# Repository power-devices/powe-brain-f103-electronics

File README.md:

# Welcome to the Power BrainF103 electronics repository

I teach power electronics and I want to provide my students the best experience possible. This is the reason I created this project. I intend to allow people to produce power electronics devices at an extreme low cost. This board required 4 layers, but this is no problem today due to [JLCPCB](https://jlcpcb.com/) or other manufacturers.

So far, the project is divided into 3 pieces:

 1. Power supply: used to delivery power the other boards, it is compatible with mono-three phase up to 220 VAC
 2. Power bullet: a three phase h-bridge, simple as that
 3. Power brain F103: the main controller

# Disclaimer

I provide no warranty at all. Use it at your own risk!

# What will I find here?

You will find the design and production files. To edit the schematic/board you will need to install Kicad. I used version 7 to create this board.

# What can I do with this?

In this repository the board design and production files are stored. You are welcome to download/distribute it, use it, whatever.

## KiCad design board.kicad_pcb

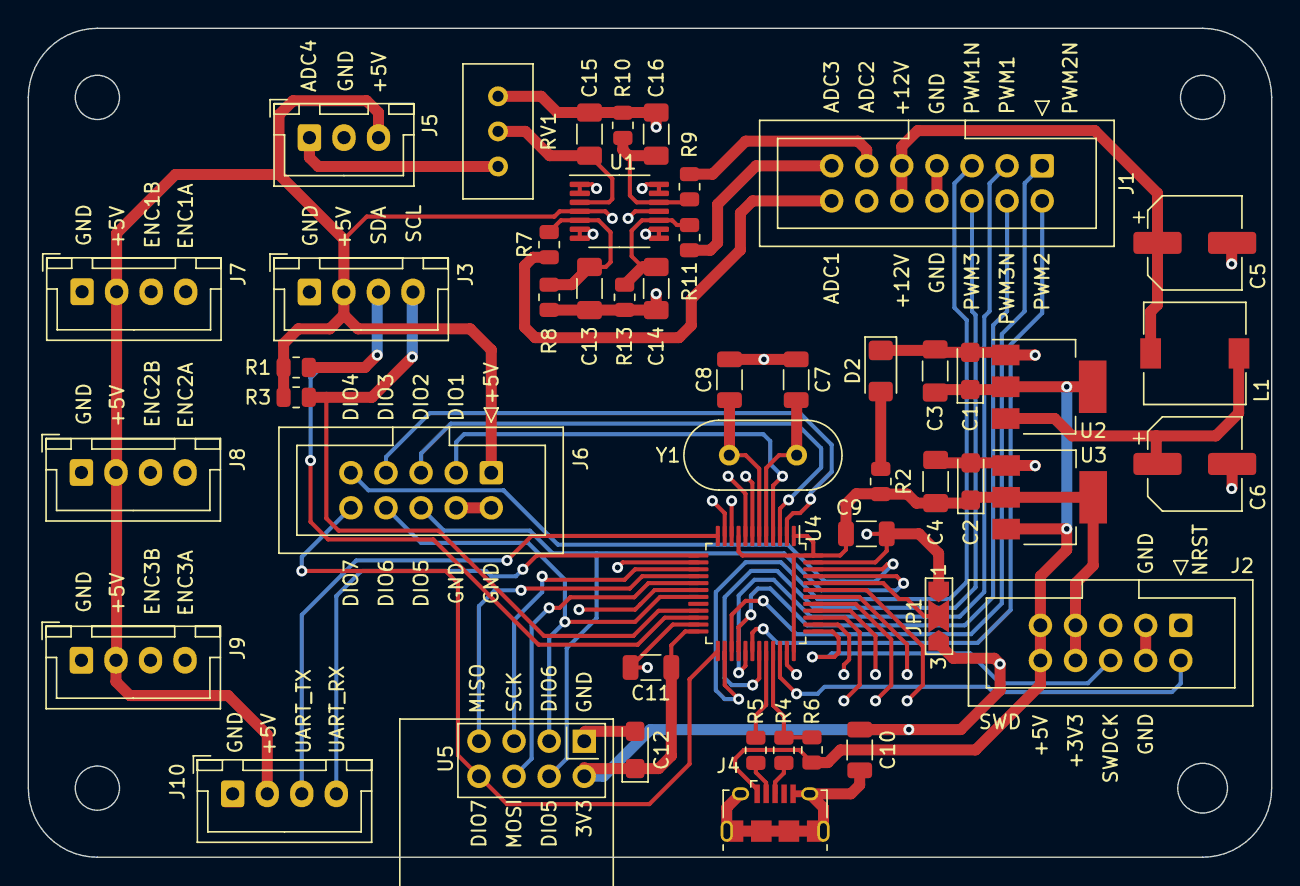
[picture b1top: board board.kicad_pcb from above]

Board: 4 copper layers, 90.0 x 60.0 mm, 48 parts (0 on the bottom side), 54 nets.

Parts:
C1, C2, C12: 10uF; CP_EIA-3216-18_Kemet-A
C3, C4: 1uF; C_1206_3216Metric_Pad1.33x1.80mm_HandSolder
C5, C6: 100uF; CP_Elec_6.3x7.7
C7, C8: 22pF; C_1206_3216Metric
C9: 1uF; C_1206_3216Metric
C10, C11: 100nF; C_1206_3216Metric
C13, C14, C15, C16: 10nF; C_1206_3216Metric_Pad1.33x1.80mm_HandSolder
D2: LED; LED_1206_3216Metric_Pad1.42x1.75mm_HandSolder
J1: Conn_02x07_Odd_Even; IDC-Header_2x07_P2.54mm_Vertical
J2: SWD; IDC-Header_2x05_P2.54mm_Vertical
J3: I2C; JST_XH_B4B-XH-A_1x04_P2.50mm_Vertical
J4: USB_B_Micro; USB_Micro-B_Amphenol_10118194_Horizontal
J5: ADC_CH4; JST_XH_B3B-XH-A_1x03_P2.50mm_Vertical
J6: GPIO; IDC-Header_2x05_P2.54mm_Vertical
J7, J8, J9: ENCODER; JST_XH_B4B-XH-A_1x04_P2.50mm_Vertical
J10: UART; JST_XH_B4B-XH-A_1x04_P2.50mm_Vertical
JP1: SolderJumper-3_P2.0mm_Open_TrianglePad1.0x1.5mm_NumberLabels
L1: 100uH; L_7.3x7.3_H4.5
R1, R3: 3k3; R_0805_2012Metric
R2: 470R; R_0805_2012Metric
R4, R5: 22R; R_0805_2012Metric
R6: 1k5; R_0805_2012Metric
R7, R9, R11: 47k; R_0805_2012Metric
R8, R10, R13: 91k; R_0805_2012Metric
RV1: 10k; Potentiometer_Bourns_3296W_Vertical
U1: LM324; TSSOP-14_4.4x5mm_P0.65mm
U2: AMS1117-5.0; SOT-223-3_TabPin2
U3: AMS1117-3.3; SOT-223-3_TabPin2
U4: STM32F103C8Tx; LQFP-48_7x7mm_P0.5mm
U5: NRF24L01; nRF24L01_Breakout
Y1: 16MHz; Crystal_HC49-4H_Vertical

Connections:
+3V3: C2.1, C4.1, C9.1, C10.1, C11.1, C12.1, J2.7, J2.8, JP1.3 (B), R2.2, U3.2 (VO), U4.1 (VBAT), U4.9 (VDDA), U4.24 (VDD), U4.36 (VDD), U4.48 (VDD), U5.2 (VCC)
+5V: C1.1, C3.1, J2.9, J2.10, J3.2, J4.1 (VBUS), J5.3, J6.1, J7.2, J8.2, J9.2, J10.2, R1.1, R3.1, R6.2, U1.4 (V+), U2.2 (VO), U3.3 (VI)
+12V: C6.1, L1.2, U2.3 (VI)
/AD4: J5.1, RV1.1
/ADC_CH1: U1.13 (-), U1.14, U4.10 (PA0)
/ADC_CH2: U1.8, U1.9 (-), U4.11 (PA1)
/ADC_CH3: U1.6 (-), U1.7, U4.14 (PA4)
/ADC_CH4: U1.1, U1.2 (-), U4.18 (PB0)
/BOOT0: JP1.2 (C), U4.44 (BOOT0)
/DRIVE1_GATE_HIGH: J1.3, U4.29 (PA8)
/DRIVE1_GATE_LOW: J1.5, U4.26 (PB13)
/DRIVE1_SENSE_IOUT: J1.14, R7.2
/DRIVE2_GATE_HIGH: J1.2, U4.30 (PA9)
/DRIVE2_GATE_LOW: J1.1, U4.27 (PB14)
/DRIVE2_SENSE_IOUT: J1.11, R9.2
/DRIVE3_GATE_HIGH: J1.6, U4.31 (PA10)
/DRIVE3_GATE_LOW: J1.4, U4.28 (PB15)
/ENC1_CHA: J7.4, U4.42 (PB6)
/ENC1_CHB: J7.3, U4.43 (PB7)
/ENC2_CHA: J8.4, U4.38 (PA15)
/ENC2_CHB: J8.3, U4.39 (PB3)
/ENC3_CHA: J9.4, U4.40 (PB4)
/ENC3_CHB: J9.3, U4.41 (PB5)
/GPIO_CH1: J6.3, U4.4 (PC15)
/GPIO_CH2: J6.5, U4.3 (PC14)
/GPIO_CH3: J6.7, U4.2 (PC13)
/GPIO_CH4: J6.9, U4.46 (PB9)
/GPIO_CH5: J6.6, U4.45 (PB8), U5.4 (~CSN)
/GPIO_CH6: J6.8, U4.19 (PB1), U5.3 (CE)
/GPIO_CH7: J6.10, U4.25 (PB12), U5.8 (IRQ)
/I2C_SCL: J3.4, R3.2, U4.21 (PB10)
/I2C_SDA: J3.3, R1.2, U4.22 (PB11)
/NRST: J2.1, U4.7 (NRST)
/POWER_12V: C5.1, J1.9, J1.10, L1.1
/SENSE_VBUS: J1.13, R11.2
/SPI_MISO: U4.16 (PA6), U5.7 (MISO)
/SPI_MOSI: U4.17 (PA7), U5.6 (MOSI)
/SPI_SCK: U4.15 (PA5), U5.5 (SCK)
/SWDCK: J2.6, U4.37 (PA14)
/SWDIO: J2.2, U4.34 (PA13)
/UART_RX: J10.4, U4.13 (PA3)
/UART_TX: J10.3, U4.12 (PA2)
/USB+: R4.1, R6.1, U4.33 (PA12)
/USB-: R5.1, U4.32 (PA11)
/XTAL1: C7.1, U4.5 (PD0), Y1.1
/XTAL2: C8.1, U4.6 (PD1), Y1.2
GND: C1.2, C2.2, C3.2, C4.2, C5.2, C6.2, C7.2, C8.2, C9.2, C10.2, C11.2, C12.2, C13.2, C14.2, C15.2, C16.2, D2.1 (K), J1.7, J1.8, J2.3, J2.4, J3.1, J4.5 (GND), J4.6 (Shield), J5.2, J6.2, J6.4, J7.1, J8.1, J9.1, J10.1, JP1.1 (A), R8.2, R10.2, R13.2, RV1.3, U1.11 (V-), U2.1 (GND), U3.1 (GND), U4.8 (VSSA), U4.23 (VSS), U4.35 (VSS), U4.47 (VSS), U5.1 (GND)
unnamed: D2.2 (A), R2.1
unnamed: J4.3 (D+), R4.2
unnamed: J4.2 (D-), R5.2
unnamed: C15.1, RV1.2, U1.3 (+)
unnamed: C13.1, R7.1, R8.1, U1.5 (+)
unnamed: C14.1, R11.1, R13.1, U1.10 (+)
unnamed: C16.1, R9.1, R10.1, U1.12 (+)

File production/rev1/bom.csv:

Designator,Footprint,Quantity,Value,LCSC Part #
"C1, C12, C2",CP_EIA-3216-18_Kemet-A,3,10uF,
"C10, C11",1206,2,100nF,
"C13, C14, C15, C16",1206,4,10nF,
"C3, C4, C9",1206,3,1uF,
"C5, C6",CP_Elec_6.3x7.7,2,100uF,
"C7, C8",1206,2,22pF,
D2,1206,1,LED,
J1,IDC-Header_2x07_P2.54mm_Vertical,1,Conn_02x07_Odd_Even,
J10,JST_XH_B4B-XH-A_1x04_P2.50mm_Vertical,1,UART,
J2,IDC-Header_2x05_P2.54mm_Vertical,1,SWD,
J3,JST_XH_B4B-XH-A_1x04_P2.50mm_Vertical,1,I2C,
J4,USB_Micro-B_Amphenol_10118194_Horizontal,1,USB_B_Micro,
J5,JST_XH_B3B-XH-A_1x03_P2.50mm_Vertical,1,ADC_CH4,
J6,IDC-Header_2x05_P2.54mm_Vertical,1,GPIO,
"J7, J8, J9",JST_XH_B4B-XH-A_1x04_P2.50mm_Vertical,3,ENCODER,
JP1,SolderJumper-3_P2.0mm_Open_TrianglePad1.0x1.5mm_NumberLabels,1,~,
L1,L_7.3x7.3_H4.5,1,100uH,
"R1, R3",0805,2,3k3,
"R10, R13, R8",0805,3,91k,
"R11, R7, R9",0805,3,47k,
R2,0805,1,470R,
"R4, R5",0805,2,22R,
R6,0805,1,1k5,
RV1,Potentiometer_Bourns_3296W_Vertical,1,10k,
U1,TSSOP-14_4.4x5mm_P0.65mm,1,LM324,
U2,SOT-223-3_TabPin2,1,AMS1117-5.0,
U3,SOT-223-3_TabPin2,1,AMS1117-3.3,
U4,LQFP-48_7x7mm_P0.5mm,1,STM32F103C8Tx,
U5,nRF24L01_Breakout,1,NRF24L01,
Y1,Crystal_HC49-4H_Vertical,1,16MHz,

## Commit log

2023-11-22 Added the REV1 files.
